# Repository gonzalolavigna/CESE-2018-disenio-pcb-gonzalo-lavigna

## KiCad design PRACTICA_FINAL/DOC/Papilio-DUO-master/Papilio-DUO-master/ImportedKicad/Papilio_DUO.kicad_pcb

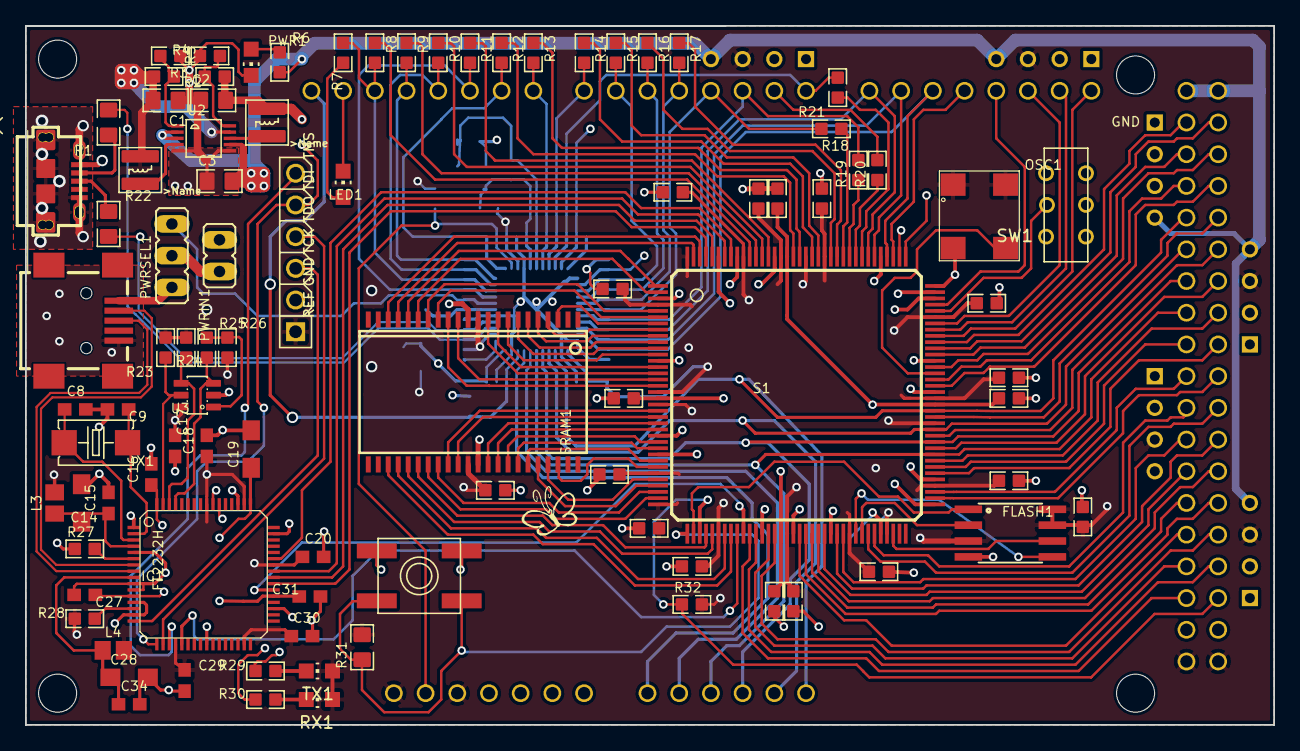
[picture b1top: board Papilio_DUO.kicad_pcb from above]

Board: 4 copper layers, 100.0 x 56.0 mm, 117 parts (0 on the bottom side), 160 nets.

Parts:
AVRUSB1: USB MICRO; CON2_USB_MICRO_B_AT
C1, C2: 22u/6V3; 0805
C3: 10u/10V; 0805
C4, C5, C6, C7, C10, C11, C12, C13, C21, C22, C23, C24, C25, C26, C32, C33, C35, C36: .1uF; 0603
C8, C9: 27pF; C603
C14, C28: 4.7uF; SMC_A
C15, C16, C17, C18, C20, C27, C29, C30, C31, C34: 0.1uF; C603
C19: 3.3uF; SMC_A
C101, C102, C105: 100n; 0603
C103, C104: 1uF; 0603
C106, C107: 22p; 0603
FLASH1: FLASH-SPI-25XXSMD1; SO08-EIAJ
FPGAUSB1: CONN_USB; CONN_USB_MINI-B
IC1: FT2232H; LQFP64
L1, L2: 3.3uH; VLS3015
L3, L4: FERRITE_BEAD603; FB603
L100: MH2029-300Y; 0805
LED1: Yellow; CHIP-LED0805
OSC1: OSC1
PWR1: Green; CHIP-LED0805
PWRIN1: JP1E; JP1
PWRSEL1: JP2E; JP2
R1, R22: 22R; 0805
R2: 6K8 1%; 0603
R3, R4, R5: 1K5 1%; 0603
R6: 1K8; 0603
R7, R32: 4.7K; 0603
R8, R9, R10, R11, R12, R13, R14, R15, R16, R17, R18, R19, R20, R21: 390; 0603
R23, R24, R26, R28: 10k; 0603
R25: 2.2k; 0603
R27: 12k 1%; 0603
R29, R30: 1K; 0603
R31: 47K; 0805
R109: 1M; 0603
R110: 10K; 0603
RX1: LEDCHIP-LED0805; CHIP-LED0805
S1: 6SLX9TQG144; TQ144
SRAM1: ISSI_SRAM_8BIT; TSOP44-II
SW1: SWITCH-2CH-6P-3010010P1; 6P-2CH-2.54-9.1X3.5X3.2+2H
SW2: EVQQ2; EVQ-Q2
TX1: LEDCHIP-LED0805; CHIP-LED0805
U1: ARDUINO_MEGA_SHIELD
U2: LTC3419MS; MSOP10
U3: 93C56B; SOT23-6
U101: ATMEGA32U4-XUMU; QFN44ML7X7
U102: ATMEGA32U4-XUAU; TQFP44-PAD
U$1: JTAG_XILINX; JTAG
U$2, U$3, U$4, U$5: STAND-OFF-TIGHT
U$7: GADGETFACTORY_LOGO
U$9: OSHW-LOGO-M
WING_POWER1, WING_POWER2, WING_POWER3, WING_POWER4, WING_POWER5, WING_POWER6: HEADER_FEMALE_4; POWER_NO_TEXT
X1: 12MHz; 4X6
Y1: 16MHz KX-7; CRYSTAL-3.2-2.5

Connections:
1.8V: C16.1, C19.+, C27.1, C31.1, IC1.12, IC1.37, IC1.49, IC1.64
1V2: C2.2, C7.1, C10.1, C13.1, C32.1, L2.2, R5.2, S1.19, S1.28, S1.52, S1.89, S1.128
3V3: C1.2, C4.1, C5.1, C6.1, C11.1, C12.1, C17.1, C18.1, C20.1, C21.1, C22.1, C23.1, C24.1, C25.1, C26.1, C29.1, C30.1, C33.1, C35.1, C36.1, C101.1, C105.1, FLASH1.3, FLASH1.7, FLASH1.8, IC1.20, IC1.31, IC1.42, IC1.50, IC1.56, L1.2, L3.2, L4.2, L100.1, OSC1.1@1, OSC1.4@4, R2.2, R23.2, R24.2, R26.2, R28.1, R31.2, R32.2, R110.2, RX1.A, S1.4, S1.18, S1.20, S1.31, S1.36, S1.42, S1.53, S1.63, S1.69, S1.76, S1.86, S1.90, S1.103, S1.122, S1.125, S1.129, S1.135, S1.144, SRAM1.11, SRAM1.33, SW1.CH2A, TX1.A, U1.3.3V, U1.3V3@1, U1.3V3@2, U1.IOREF, U2.9, U3.6, U101.2, U101.14, U101.34, U102.2, U102.14, U102.34, U$1.JTAG_REF, WING_POWER1.P3, WING_POWER2.P3, WING_POWER3.P3, WING_POWER4.P3, WING_POWER5.P3, WING_POWER6.P3
5V0: C3.2, PWRIN1.1, PWRSEL1.2, R6.2, U1.5V@0, U1.5V@1, U1.5V@2, U2.2, U2.3, U2.7, WING_POWER1.P4, WING_POWER2.P4, WING_POWER3.P4, WING_POWER4.P4, WING_POWER5.P4, WING_POWER6.P4
5V_ARDUINO: AVRUSB1.P1, PWRSEL1.3, U101.7, U102.7
5V_FT2232: FPGAUSB1.VUSB, PWRSEL1.1
/Arduino/AVCC: C104.1, L100.2, U101.24, U101.44, U102.24, U102.44
/Arduino/AVRUSB_N: R1.2, U101.3, U102.3
/Arduino/AVRUSB_P: R22.2, U101.4, U102.4
/Arduino/D+: AVRUSB1.P3, R22.1
/Arduino/D-: AVRUSB1.P2, R1.1
/Arduino/NC: U101.1, U102.1
/Arduino/UCAP: C103.1, U101.6, U102.6
/Arduino/XTAL1: C107.1, R109.1, U101.17, U102.17, Y1.1
/Arduino/XTAL2: C106.2, R109.2, U101.16, U102.16, Y1.3
/FPGA/A0: S1.7, SRAM1.3
/FPGA/A1: S1.8, SRAM1.4
/FPGA/A2: S1.9, SRAM1.5
/FPGA/A3: S1.10, SRAM1.6
/FPGA/A4: S1.11, SRAM1.7
/FPGA/A5: S1.5, SRAM1.16
/FPGA/A6: S1.2, SRAM1.17
/FPGA/A7: S1.1, SRAM1.18
/FPGA/A8: S1.143, SRAM1.19
/FPGA/A9: S1.142, SRAM1.20
/FPGA/A10: S1.43, SRAM1.26
/FPGA/A11: S1.41, SRAM1.27
/FPGA/A12: S1.40, SRAM1.28
/FPGA/A13: S1.35, SRAM1.29
/FPGA/A14: S1.34, SRAM1.30
/FPGA/A15: S1.27, SRAM1.38
/FPGA/A16: S1.29, SRAM1.39
/FPGA/A17: S1.33, SRAM1.40
/FPGA/A18: S1.32, SRAM1.41
/FPGA/A19: S1.44, SRAM1.25
/FPGA/A20: S1.30, SRAM1.42
/FPGA/D0: S1.14, SRAM1.9
/FPGA/D1: S1.15, SRAM1.10
/FPGA/D2: S1.16, SRAM1.13
/FPGA/D3: S1.17, SRAM1.14
/FPGA/D4: S1.21, SRAM1.31
/FPGA/D5: S1.22, SRAM1.32
/FPGA/D6: S1.23, SRAM1.35
/FPGA/D7: S1.24, SRAM1.36
/FPGA/FLASH_CS: FLASH1.1, S1.38
/FPGA/FLASH_SCK: FLASH1.6, S1.70
/FPGA/FLASH_SI: FLASH1.5, S1.64
/FPGA/FLASH_SO: FLASH1.2, S1.65
/FPGA/MEGA_D0: R21.1, S1.116
/FPGA/MEGA_D1: R20.1, S1.117
/FPGA/MEGA_D2: R19.1, S1.118
/FPGA/MEGA_D3: R18.1, S1.119
/FPGA/MEGA_D4: R17.1, S1.120
/FPGA/MEGA_D5: R16.1, S1.121
/FPGA/MEGA_D6: R15.1, S1.123
/FPGA/MEGA_D7: R14.1, S1.124
/FPGA/MEGA_D8: R13.1, S1.126
/FPGA/MEGA_D9: R12.1, S1.127
/FPGA/MEGA_D10: R11.1, S1.131
/FPGA/MEGA_D11: R10.1, S1.132
/FPGA/MEGA_D12: R9.1, S1.133
/FPGA/MEGA_D13: R8.1, S1.134
/FPGA/MEGA_D17: S1.111, U1.D17
/FPGA/MEGA_D18: S1.105, U1.D18
/FPGA/MEGA_D19: S1.102, U1.D19
/FPGA/MEGA_D20: S1.101, U1.D20
/FPGA/MEGA_D21: S1.100, U1.D21
/FPGA/MEGA_D22: S1.99, U1.D22
/FPGA/MEGA_D23: S1.98, U1.D23
/FPGA/MEGA_D24: S1.97, U1.D24
/FPGA/MEGA_D25: S1.95, U1.D25
/FPGA/MEGA_D26: S1.93, U1.D26
/FPGA/MEGA_D27: S1.92, U1.D27
/FPGA/MEGA_D29: S1.87, U1.D29
/FPGA/MEGA_D31: S1.84, U1.D31
/FPGA/MEGA_D33: S1.82, U1.D33
/FPGA/MEGA_D35: S1.80, U1.D35
/FPGA/MEGA_D36: S1.79, U1.D36
/FPGA/MEGA_D37: S1.78, U1.D37
/FPGA/MEGA_D38: S1.75, U1.D38
/FPGA/MEGA_D39: S1.74, U1.D39
/FPGA/MEGA_D40: S1.67, U1.D40
/FPGA/MEGA_D41: S1.66, U1.D41
/FPGA/MEGA_D42: S1.62, U1.D42
/FPGA/MEGA_D43: S1.61, U1.D43
/FPGA/MEGA_D44: S1.59, U1.D44
/FPGA/MEGA_D45: S1.58, U1.D45
/FPGA/MEGA_D46: S1.57, U1.D46
/FPGA/MEGA_D47: S1.56, U1.D47
/FPGA/MEGA_D48: S1.55, U1.D48
/FPGA/MEGA_D49: S1.51, U1.D49
/FPGA/MEGA_D50: S1.50, U1.D50
/FPGA/MEGA_D51: S1.48, U1.D51
/FPGA/MEGA_D52: S1.47, U1.D52
/FPGA/MEGA_D53: R32.1, S1.39, U1.D53
/FPGA/OSC_IN: OSC1.3@3, S1.94
/FPGA/SW1: S1.104, SW1.COM2
/FPGA/~CS: S1.12, SRAM1.8
/FPGA/~OE: S1.26, SRAM1.37
/FPGA/~WE: S1.6, SRAM1.15
/FT2232H/BC3: IC1.54, R30.1
/FT2232H/BC4: IC1.55, R29.1
/FT2232H/EECLK: IC1.62, R24.1, U3.4
/FT2232H/EECS: IC1.63, R23.1, U3.5
/FT2232H/EEDATA: IC1.61, R25.2, U3.3
/FT2232H/FTUSB_N: FPGAUSB1.D-, IC1.7
/FT2232H/FTUSB_P: FPGAUSB1.D+, IC1.8
/FT2232H/~RESET: IC1.14, R28.2
AD0-JTAG_TCK: IC1.16, S1.109, U$1.JTAG_TCK
AD1-JTAG_TDI: IC1.17, S1.110, U$1.JTAG_TDI
AD2-JTAG_TDO: IC1.18, S1.106, U$1.JTAG_TDO
AD3-JTAG_TMS: IC1.19, S1.107, U$1.JTAG_TMS
AD4-DTR: IC1.21, S1.45
ARD_RESET: R110.1, S1.139, U1.RES, U101.13, U102.13
AREF: C102.2, U1.AREF, U101.42, U102.42
ATMEGA_A0: U1.A0, U101.41, U102.41
ATMEGA_A1: U1.A1, U101.40, U102.40
ATMEGA_D0/RX: R21.2, U1.RX, U101.20, U102.20
ATMEGA_D1/TX: R20.2, U1.TX, U101.21, U102.21
ATMEGA_D2: R19.2, U1.D2, U101.29, U102.29
ATMEGA_D3: R18.2, U1.D3, U101.28, U102.28
ATMEGA_D4: R17.2, U1.D4, U101.27, U102.27
ATMEGA_D5*: R16.2, U1.D5, U101.26, U102.26
ATMEGA_D6*: R15.2, U1.D6, U101.25, U102.25
ATMEGA_D7: R14.2, U1.D7, U101.19, U102.19
ATMEGA_IO8: R13.2, U1.D8, U101.18, U102.18
ATMEGA_IO9*: R12.2, U1.D9, U101.12, U102.12
ATMEGA_IO10*: R11.2, U1.D10, U101.8, U102.8
ATMEGA_IO11*: R10.2, U1.D11, U101.10, U102.10
ATMEGA_IO12: R9.2, U1.D12, U101.11, U102.11
ATMEGA_IO13*: R7.2, R8.2, U1.D13, U101.9, U102.9
BD0_TXD/MPSSE_TCK: IC1.38, S1.46
BD1_RXD/MPSSE_TDI: IC1.39, S1.141
BD2_MPSSE_TDO: IC1.40, S1.140
BD3_MPSSE_TMS: IC1.41, S1.138
BD4-DTR: IC1.43, S1.137
GND: AVRUSB1.P5, AVRUSB1.S1, AVRUSB1.S2, AVRUSB1.S3, AVRUSB1.S4, AVRUSB1.S5, AVRUSB1.S6, C1.1, C2.1, C3.1, C4.2, C5.2, C6.2, C7.2, C8.2, C9.2, C10.2, C11.2, C12.2, C13.2, C14.-, C15.2, C16.2, C17.2, C18.2, C19.-, C20.2, C21.2, C22.2, C23.2, C24.2, C25.2, C26.2, C27.2, C28.-, C29.2, C30.2, C31.2, C32.2, C33.2, C34.2, C35.2, C36.2, C101.2, C102.1, C103.2, C104.2, C105.2, C106.1, C107.2, FLASH1.4, FPGAUSB1.GND, IC1.1, IC1.5, IC1.10, IC1.11, IC1.13, IC1.15, IC1.25, IC1.35, IC1.47, IC1.51, LED1.C, OSC1.2@2, PWR1.C, PWRIN1.2, R3.1, R4.1, R27.1, S1.3, S1.13, S1.25, S1.49, S1.54, S1.60, S1.68, S1.73, S1.77, S1.91, S1.96, S1.108, S1.113, S1.130, S1.136, SRAM1.12, SRAM1.34, SW1.CH2B, SW2.B, SW2.B', U1.GND@0, U1.GND@1, U1.GND@2, U1.GND@3, U1.GND@4, U2.5, U2.6, U3.2, U101.5, U101.15, U101.23, U101.33, U101.35, U101.43, U101.EXP, U102.5, U102.15, U102.23, U102.33, U102.35, U102.43, U102.P$1, U$1.JTAG_GND, WING_POWER1.P1, WING_POWER2.P1, WING_POWER3.P1, WING_POWER4.P1, WING_POWER5.P1, WING_POWER6.P1, Y1.2, Y1.4
MEGA_D14: S1.115, U1.D14, U101.30, U102.30
MEGA_D15: S1.114, U1.D15, U101.31, U102.31
MEGA_D16: S1.112, U1.D16, U101.32, U102.32
MEGA_D28/A5: S1.88, U1.A5, U1.D28, U101.36, U102.36
MEGA_D30/A4: S1.85, U1.A4, U1.D30, U101.37, U102.37
MEGA_D32/A3: S1.83, U1.A3, U1.D32, U101.38, U102.38
MEGA_D34/A2: S1.81, U1.A2, U1.D34, U101.39, U102.39
unnamed: C8.1, IC1.3, X1.2
unnamed: C9.1, IC1.2, X1.1
unnamed: C14.+, C15.1, IC1.4, L3.1
unnamed: C28.+, C34.1, IC1.9, L4.1
unnamed: IC1.6, R27.2
unnamed: L1.1, U2.4
unnamed: L2.1, U2.8
unnamed: LED1.A, R7.1
unnamed: PWR1.A, R6.1
unnamed: R2.1, R3.2, U2.1
unnamed: R4.2, R5.1, U2.10
unnamed: R25.1, R26.1, U3.1
unnamed: R29.2, TX1.C
unnamed: R30.2, RX1.C
unnamed: R31.1, S1.37, SW2.A, SW2.A'
unnamed: U101.22, U102.22

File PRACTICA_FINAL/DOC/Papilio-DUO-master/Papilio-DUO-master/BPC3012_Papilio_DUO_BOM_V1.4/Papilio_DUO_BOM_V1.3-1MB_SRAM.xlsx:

Qty-1 | Part References | Value | Package | Mfg Part Num | Mfg Name | VID | Vendor Part Num | Description | Pkg Code | XREF
1 | PWR | Green | CHIP-LED0805 | LTST-C171EKT | LITE-ON INC (VA) | DK | 160-1422-1-ND | LED RED ORAN CLEAR THIN 0805 SMD | 805 | REF100
1 | R31 | 47K | 805 | RMCF0805JT47K0 | Stackpole Electronics Inc | DK | RMCF0805JT47K0CT-ND | RES 47K OHM 1/8W 5% 0805 SMD | 805 | REF109
2 | RX, TX |  | LED-805 | LTST-C170KGKT | LITE-ON INC (VA) | DK | 160-1414-1-ND | LED GREEN CLEAR 0805 SMD | 805 | REF111
1 | LED | Yellow | CHIPLED_0805 | LTST-C170KGKT | LITE-ON INC (VA) | DK | 160-1414-1-ND | LED GREEN CLEAR 0805 SMD | 805 | REF111
1 | S1 | 6SLX9TQG144 | TQ144 | XC6SLX9-2TQG144C | XILINX INC | DK | 122-1745-ND | IC FPGA SPARTAN-6 9K 144TQFP | 144TQFP | REF112
1 | U3 | 93C46B | SOT23-6 | 93C46BT-I/OT | MICROCHIP TECHNOLOGY (VA) | DK | 93C46BT-I/OTCT-ND | IC EEPROM 1KBIT 2MHZ SOT23-6 | SOT23 | REF113
1 | FLASH | FLASH-SPI-25XXSMD1 | SO08-EIAJ | MX25L6445EM2I-10G | Macronix | DK | 1092-1065-ND | IC FLASH SER 64MB 104MHZ 8SOIC | 8SOIC | REF115
1 | FPGAUSB | CONN_USB | CONN_USB_MINI-B | USB-M26FTR | On Shore Technology Inc | DK | ED2992CT-ND | MINI-USB-B Connector | * | REF116
1 | SW2 | EVQQ2 | EVQ-Q2 | PTS525SM10SMTR LFS | C&K Components | DK | CKN9104CT-ND | SWITCH TACTILE SPST-NO 0.05A 12V | * | REF119
2 | L1, L2 | 3.3uH | VLS3015 | VLS3015T-3R3M1R2 | TDK CORPORATION (VA) | DK | 445-3696-1-ND | INDUCTOR POWER 3.3UH 1.2A SMD | SMD | REF120
1 | U2 | LTC3419EMS | MSOP10 | LTC3419EMS#PBF | LINEAR TECHNOLOGY | DK | LTC3419EMS#PBF-ND | IC REG BUCK SYNC ADJ 0.6A 10MSOP | 10MSOP | REF121
2 | C1, C2 | 22u/6V3 | 805 | GRM21BR60J226ME39L | MURATA ELECTRONICS (VA) | DK | 490-1719-1-ND | CAP CER 22UF 6.3V 20% X5R 0805 | 805 | REF122
3 | R3, R4, R5 | 1K5 1% | 603 | CRCW06031K50FKEA | VISHAY DALE (VA) | DK | 541-1.50KHCT-ND | RES 1.50K OHM 1/10W 1% 0603 SMD | 603 | REF123
1 | R2 | 6K8 1% | 603 | CRCW06036K80FKEA | VISHAY DALE (VA) | DK | 541-6.80KHCT-ND | RES 6.80K OHM 1/10W 1% 0603 SMD | 603 | REF124
2 | C8, C9 | 27pF | C603 | CL10C270JB8NNNC | Samsung | DK | 1276-1086-1-ND | CAP CER 27PF 50V 5% NP0 0603 | 603 | REF125
2 | C106, C107 | 22p | C0603K | C1608C0G1H220J080AA | TDK CORPORATION (VA) | DK | 445-1273-1-ND | CAP CER 22PF 50V 5% NP0 0603 | 603 | REF126
2 | C103, C104 | 1uF | C0603K | C1608X5R1A105K080AC | TDK CORPORATION (VA) | DK | 445-1321-1-ND | CAP CER 1UF 10V 10% X5R 0603 | 603 | REF127
1 | C19 | 3.3uF | SMC_A | T491A335K016AT7280 | Kemet | DK | 399-10124-1-ND | CAP TANT 3.3UF 16V 10% 1206 | 1206 | REF129
2 | C14, C28 | 4.7uF | SMC_A | T491A475M010AT | Kemet | DK | 399-3698-1-ND | CAP TANT 4.7UF 10V 20% 1206 | 1206 | REF130
1 | AVRUSB | USB MICRO | CON2_USB_MICRO_B_AT | 10118193-0001LF | FCI | DK | 609-4616-1-ND | CONN USB MICRO B RECPT SMT R/A - Leonardo | * | REF131
1 | IC1 | FT2232H | LQFP64 | FT2232HL-REEL | FTDI (VA) | DK | 768-1024-1-ND | IC USB HS DUAL UART/FIFO 64-LQFP | * | REF133
2 | L3, L4 |  | FB603 | MMZ1608R600A | TDK CORPORATION (VA) | DK | 445-2182-1-ND | FERRITE CHIP BEAD 60 OHM SMD | 603 | REF134
1 | L100 | MH2029-300Y | 805 | MH2029-300YCT-ND | Bourns Inc. | DK | MH2029-300Y | BEAD FERRITE 30 OHM 3A - Leonardo | 805 | REF135
1 | PWRIN |  | JP1 | 68000-102HLF | BERGSTICK | DK | 609-3500-ND | 1x2 Male Pin Header .1 | * | REF136
1 | PWRSEL |  | JP2 | 68000-103HLF | BERGSTICK | DK | 609-3461-ND | 1x3 Male Pin Header .1 | * | REF137
2 | R1, R22 | 22R | 805 | RMCF0805JT22R0 | StackPole | DK | RMCF0805JT22R0CT-ND | RES 22 OHM 1/8W 5% 0805 | 805 | REF138
1 | R6 | 1K8 | 603 | RMCF0603JT1K80 | StackPole | DK | RMCF0603JT1K80CT-ND | RES 1.8K OHM 1/10W 5% 0603 | 603 | REF139
1 | R7 | 1K | 603 | RMCF0603JT1K00 | StackPole | DK | RMCF0603JT1K00CT-ND | RES 1K OHM 1/10W 5% 0603 | 603 | REF140
14 | R8, R9, R10, R11, R12, R13, R14, R15, R16, R17, R18, R19, R20, R21 | 390 | 603 | RMCF0603JT390R | StackPole | DK | RMCF0603JT390RCT-ND | RES 390 OHM 1/10W 5% 0603 | 603 | REF141
1 | R110 | 10K | 603 | RMCF0603JT10K0 | StackPole | DK | RMCF0603JT10K0CT-ND | RES 10K OHM 1/10W 5% 0603 | 603 | REF142
4 | R23, R24, R26, R28 | 10k | R603 | RMCF0603JT10K0 | StackPole | DK | RMCF0603JT10K0CT-ND | RES 10K OHM 1/10W 5% 0603 | 603 | REF142
1 | R25 | 2.2k | R603 | RMCF0603JT2K20 | StackPole | DK | RMCF0603JT2K20CT-ND | RES 2.2K OHM 1/10W 5% 0603 | 603 | REF143
1 | R27 | 12k 1% | R603 | RMCF0603FT12K0 | StackPole | DK | RMCF0603FT12K0CT-ND | RES 12K OHM 1/10W 1% 0603 | 603 | REF144
2 | R29, R30 | 470 | R603 | RMCF0603JT470R | StackPole | DK | RMCF0603JT470RCT-ND | RES 470 OHM 1/10W 5% 0603 | 603 | REF145
1 | R32 | 4.7K | 603 | RMCF0603JT4K70 | StackPole | DK | RMCF0603JT4K70CT-ND | RES 4.7K OHM 1/10W 5% 0603 | 603 | REF146
1 | R109 | 1M | R0603-ROUND | RMCF0603JT1M00 | StackPole | DK | RMCF0603JT1M00CT-ND | RES 1M OHM 1/10W 5% 0603 | 603 | REF147
1 | SRAM | 1MB-SRAM | TSOP44-II | IS61WV10248BLL-10TLI | ISSI | DK | 706-1056-ND | 8MBIT 10NS 44TSOP - 1MB - Papilio DUO | 44TSOP | REF153
1 | SW1 | SWITCH-2CH-6P-3010010P1 | 6P-2CH-2.54-9.1X3.5X3.2+2H | EG1271 | E-Switch | DK | EG1918-ND | SWITCH SLIDE SPDT L=2MM 30V - Seeed Part Library | * | REF158
1 | U101 | ATMEGA32U4-XUMU | QFN44ML7X7 | ATMEGA32U4RC-MUR | Atmel | DK | ATMEGA32U4RC-MURCT-ND | IC MCU 8BIT 32KB FLASH 44QFN - Papilio DUO | 44QFN | REF159
1 | X1 | 12MHz | 4X6 | ABM7-12.000MHZ-D2Y-T | Abracon Corporation | DK | 535-9836-1-ND | CRYSTAL 12MHZ 18PF SMD - 4x6 - FT2232H | * | REF160
1 | Y1 | 16MHz KX-7 | CRYSTAL-3.2-2.5 | ABM8G-16.000MHZ-B4Y-T | Abracon Corporation | DK | 535-10289-1-ND | CRYSTAL 16MHZ 10PF SMD - Leonardo Crystal | * | REF161
3 | HEADER_0-7, HEADER_8-AREF, HEADER_14-21 | HEADER_FEMALE_8 | * | PPTC081LFBN-RC | Sullins Connector | DK | S7006-ND | CONN HEADER FEMALE 8POS .1"" TIN | * | REF162
1 | HEADER_NC-IOREF | HEADER_FEMALE_7 | * | PPTC071LFBN-RC | Sullins Connector | DK | S7005-ND | CONN HEADER FEMALE 7POS .1"" TIN | * | REF163
1 | HEADER_ANALOG | HEADER_FEMALE_6 | * | PPTC061LFBN-RC | Sullins Connector | DK | S7004-ND | CONN HEADER FEMALE 6POS .1"" TIN | * | REF164
6 | WING_POWER1, WING_POWER2, WING_POWER3, WING_POWER4, WING_POWER5, WING_POWER6 | HEADER_FEMALE_4 | POWER_NO_TEXT | PPTC041LFBN-RC | Sullins Connector | DK | S7002-ND | CONN HEADER FEMALE 4POS .1"" TIN | * | REF165
2 | HEADER_C, HEADER_D | HEADER_FEMALE_19 | * | PPTC191LFBN-RC | Sullins Connector | DK | S7017-ND | CONN HEADER FEMALE 19POS.1"" TIN | * | REF166
1 | C3 | 10u/10V | 805 | C0805C106K9PACTU | Kemet | DK | 399-3138-1-ND | CAP CERAMIC 10UF 6.3V X5R 0805 | 805 | REF72
18 | C4, C5, C6, C7, C10, C11, C12, C13, C21, C22, C23, C24, C25, C26, C32, C33, C35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 | .1uF | 603 | GRM188F51E104ZA01D | MURATA ELECTRONICS (VA) | DK | 490-1575-1-ND | CAP CER .1UF 25V Y5V 0603 | 603 | REF96
10 | C15, C16, C17, C18, C20, C27, C29, C30, C31, C34 | 0.1uF | C603 | GRM188F51E104ZA01D | MURATA ELECTRONICS (VA) | DK | 490-1575-1-ND | CAP CER .1UF 25V Y5V 0603 | 603 | REF96
3 | C101, C102, C105 | 100n | C0603K | GRM188F51E104ZA01D | MURATA ELECTRONICS (VA) | DK | 490-1575-1-ND | CAP CER .1UF 25V Y5V 0603 | 603 | REF96
1 | OSC |  | OSC1 | ASV-32.000MHZ-E-T | Abracon Corporation | DK | 535-10082-1-ND | OSC 32.0000 MHZ 3.3V SMT | SMT | REF99

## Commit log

2018-09-27 Se agregan los primeros pasos en la practica 01 de PCBs
2018-09-28 Se genera la netlist para la clase 02
2018-10-05 Se finaliza la practica de PCB la 01 y tambien se agrega informacion de la Papillio Duo
2018-10-06 Agregado de liberias, exportacion proyecto a Altium Tratando de encontrar Aduino Mega Shield para Kicad con nombres parecidos capaz convenga usarla.
2018-10-06 SE agrega a la libreria una resistencia normal 0603 no se porque las importo mal el kICAD. Genero el mismo simbolo. Se agrega el esquematico bajado de la pagina. Se genera la pagina de Arduino en el 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
2018-10-06 Se agrega exportacion del Eagle hecho por el Kicad.
2018-10-07 Terminada la hoja del FTDI y POWER y Arduino.bak FPGA terminado Power y Pheripheral. Lo principal de la cuestion del bnloque FPGA estan puestos los componentyes. Queda revisar globales y pasarlas a l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
2018-10-07 Tambien se tienen que cambiar algunas cosas de la libreria digase algu8nops nombres que aparecieron con @ y tambien largos y nombres y formas. De lo visto hasta el momento los nombres coinciden bien 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
2018-10-08 Actualizado el esquematico de la FPGA, terminada todas las conexiones quedan los pines jerarquicos nada mas a nivel esquematico.
2018-10-13 Actualizado el esquematico se enumera igual que el pdf. Se asignan todas las huellas lo unico que falta es la huella de un Arduino superpuesto Se corre DRC de esquematico y tambien se pasa a .NET y s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
2018-10-16 Ubicacion de los componentes. Todos los modelos 3D. Agregados los componentes que no estaban en la libreria de Kicad que fueron bastantes.
2018-10-16 Agregados ultimos modelos 3D y tambien los agujeros de sujecion hasta aca estaria el trabajo.
2018-10-16 Actualizado rotulos Agregado agujeros y cotas. Esta el trabajo segun lo que se habla con Diego. Esta para revisarse.
2018-10-19 Se agregan las imagenes de las vistas en 3D. Tambien se configurar los coopper pour y ademas se tiran algunas pistas y algunas vias termicas.
2018-10-19 Se conecta la señal de JTAG_REG del conector JTAG estaba conectado en el PCB y en el esquematico no se vio conectado. Se hace la modificacion en el esquematico y se hace backannotate al PCB:
2018-10-19 Se agrega un mensaje en el top indicando donde se encuentra la informacion del HW el correspondiente link de la Papillio DUE.
2018-10-19 Se borra el autosave del repositorio.
2018-10-27 Se agrega Logos y Simbolos Se agrega fiduciales Se acomoda serigrafia para que sea visible y coherente Se agrega libreria de giduciales Se crea simbolo para el logo
2018-11-15 Se actualizan en el esquematico recomendacion de Diego Brengi. Tambien se importa al PCB para verificar que no hayan habido cambios en las netlist.
2018-11-18 Se actualizan correcciones en el PCB

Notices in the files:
PRACTICA_FINAL/DOC/Papilio-DUO-master/Papilio-DUO-master/ImportedKicad/Papilio_DUO.kicad_pcb:
Copyright 2014
CC-BY-SA 4.0
